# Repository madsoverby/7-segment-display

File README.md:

# ESP32 7-Segment Display Controller

A 7-segment display controller implemented on an ESP32 development board.

This project demonstrates direct GPIO-driven segment control without external driver ICs.  
It is designed specifically for ESP32 hardware.

---

## 🔍 Technical Overview

The system controls 7 LEDs each segment is individual driving via ESP32 GPIO pins.

A push button is connected for user interaction (e.g., incrementing displayed values).

---

## 🧰 Hardware Requirements

- ESP32 development board
- 7 LEDs
- 220–330Ω current-limiting resistors
- Push button
- Breadboard and jumper wires

---

## 🔌 GPIO Mapping

| Segment | GPIO |
|---------|------|
| A | 12 |
| B | 14 |
| C | 32 |
| D | 33 |
| E | 25 |
| F | 26 |
| G | 27 |
| Button | 0 |
| DS18B20 | 4|

⚠️ This configuration is designed for ESP32.  
Using another board requires updating the pin configuration in the source code.

---

## ⚙️ Environment Setup

1. Install Arduino IDE
2. Add ESP32 board support:
   - File → Preferences
   - Add:
     https://raw.githubusercontent.com/espressif/arduino-esp32/gh-pages/package_esp32_index.json
3. Install **ESP32 by Espressif Systems**
4. Select your ESP32 board under Tools → Board
5. To use the DS18B20 temperature sensor, you must install the OneWire and DallasTemperature libraries.

---

## 🚀 Build & Upload

1. Open the `.ino` file
2. Select correct board and serial port
3. Upload to ESP32

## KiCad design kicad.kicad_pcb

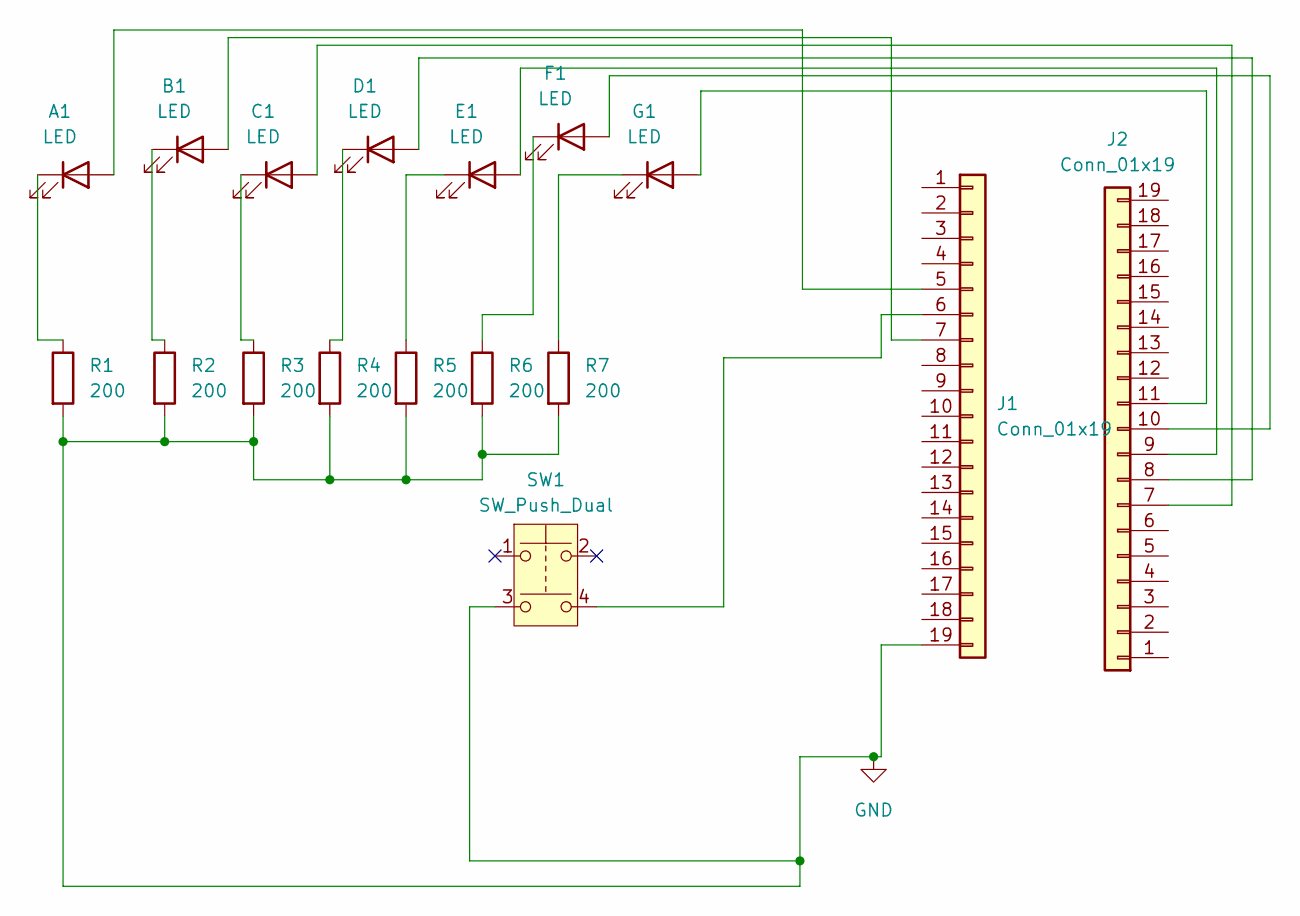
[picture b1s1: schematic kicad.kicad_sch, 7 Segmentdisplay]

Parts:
A1: LED; LED_D3.0mm
B1: LED; LED_D3.0mm
C1: LED; LED_D3.0mm
D1: LED; LED_D3.0mm
E1: LED; LED_D3.0mm
F1: LED; LED_D3.0mm
G1: LED; LED_D3.0mm
J1, J2: Conn_01x19; PinSocket_1x19_P2.54mm_Vertical
R1, R2, R3, R4, R5, R6, R7: 200; R_Axial_DIN0309_L9.0mm_D3.2mm_P12.70mm_Horizontal
SW1: SW_Push_Dual; SW_PUSH_6mm_H5mm

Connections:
GND: J1.19, R1.2, R2.2, R3.2, R4.2, R5.2, R6.2, R7.2, SW1.3
unnamed: A1.2 (A), J1.5
unnamed: A1.1 (K), R1.1
unnamed: B1.2 (A), J1.7
unnamed: B1.1 (K), R2.1
unnamed: C1.2 (A), J2.7
unnamed: C1.1 (K), R3.1
unnamed: D1.2 (A), J2.8
unnamed: D1.1 (K), R4.1
unnamed: E1.2 (A), J2.9
unnamed: E1.1 (K), R5.1
unnamed: F1.2 (A), J2.10
unnamed: F1.1 (K), R6.1
unnamed: G1.2 (A), J2.11
unnamed: G1.1 (K), R7.1
unnamed: J1.6, SW1.4

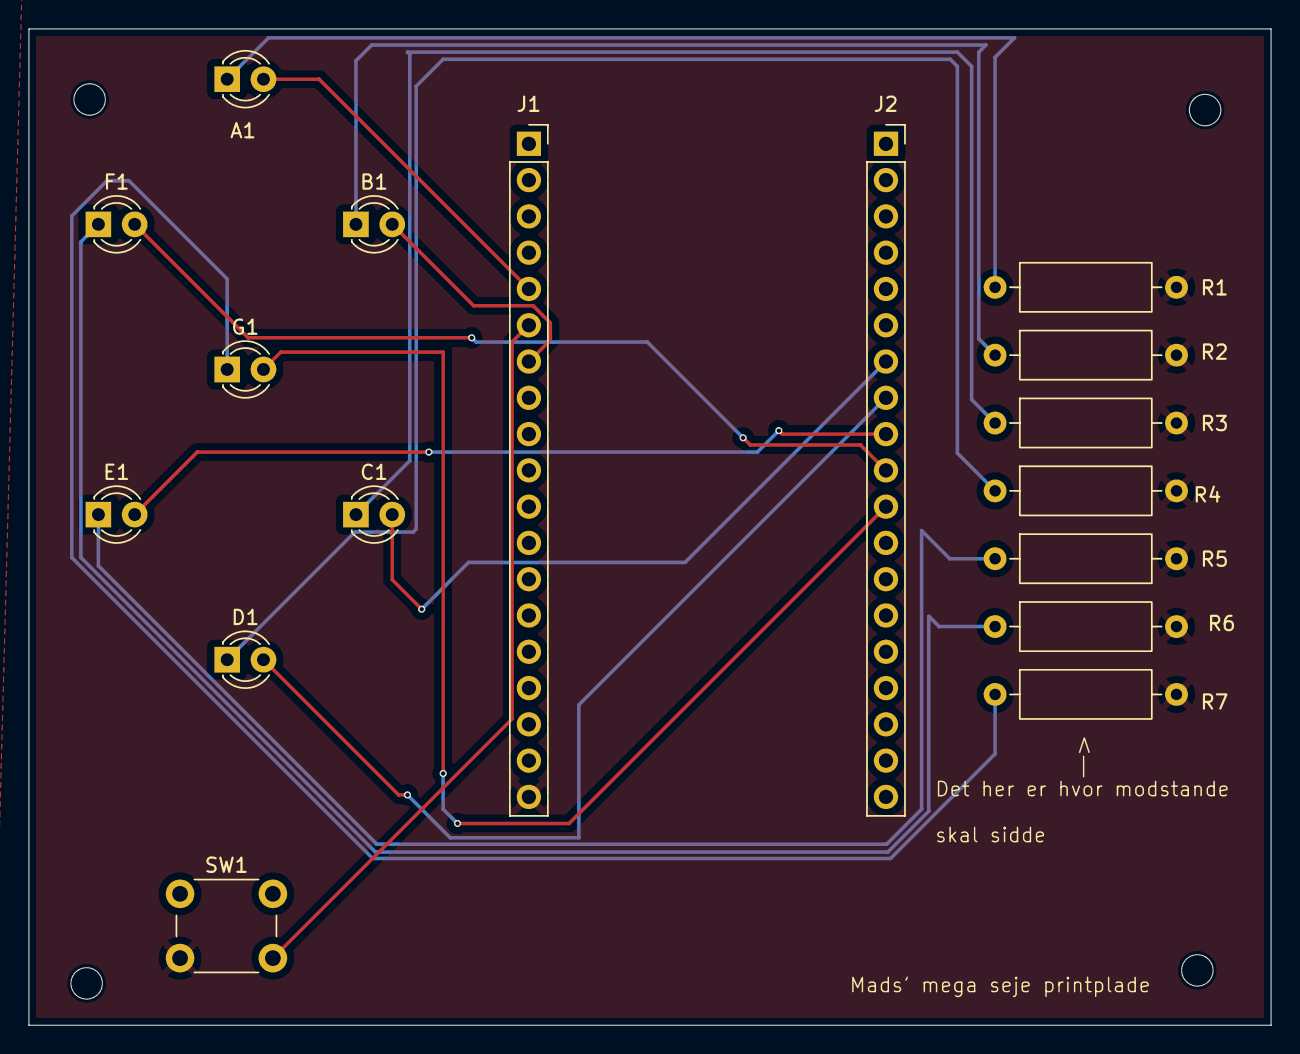
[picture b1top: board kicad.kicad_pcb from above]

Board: 2 copper layers, 87.0 x 69.8 mm, 17 parts (0 on the bottom side), 16 nets.

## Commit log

2026-02-16 first commít
2026-02-16 addet a .gitignore and a README
2026-02-16 Remove KiCad backup files
2026-02-16 deletet all ki cad files
2026-02-17 made som chagdes
2026-02-17 chagde the readme and translatet comments to english
